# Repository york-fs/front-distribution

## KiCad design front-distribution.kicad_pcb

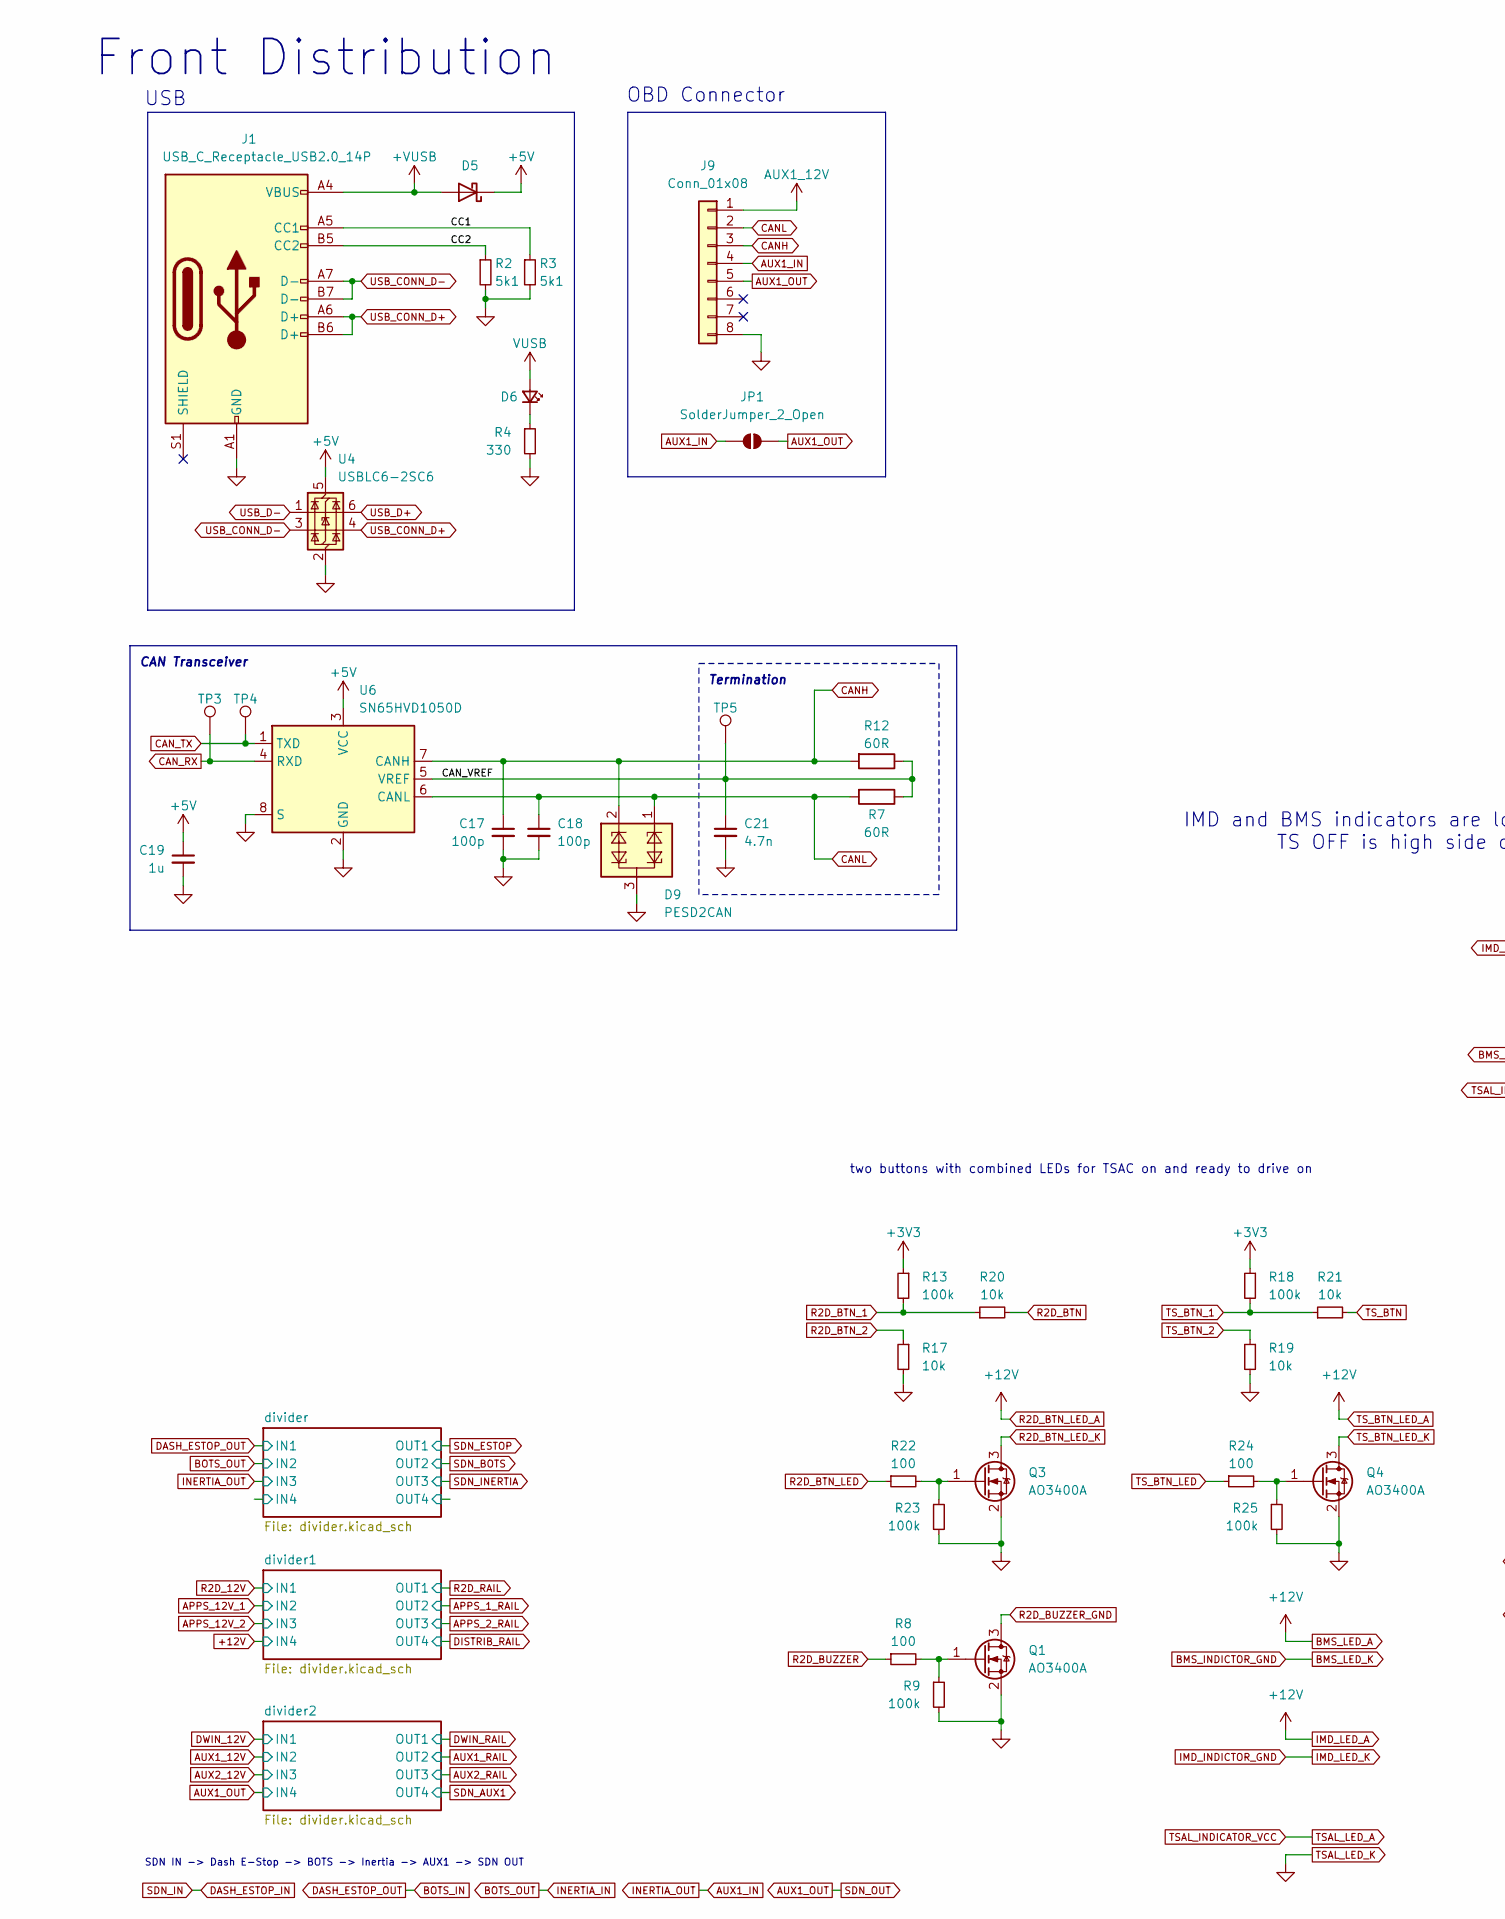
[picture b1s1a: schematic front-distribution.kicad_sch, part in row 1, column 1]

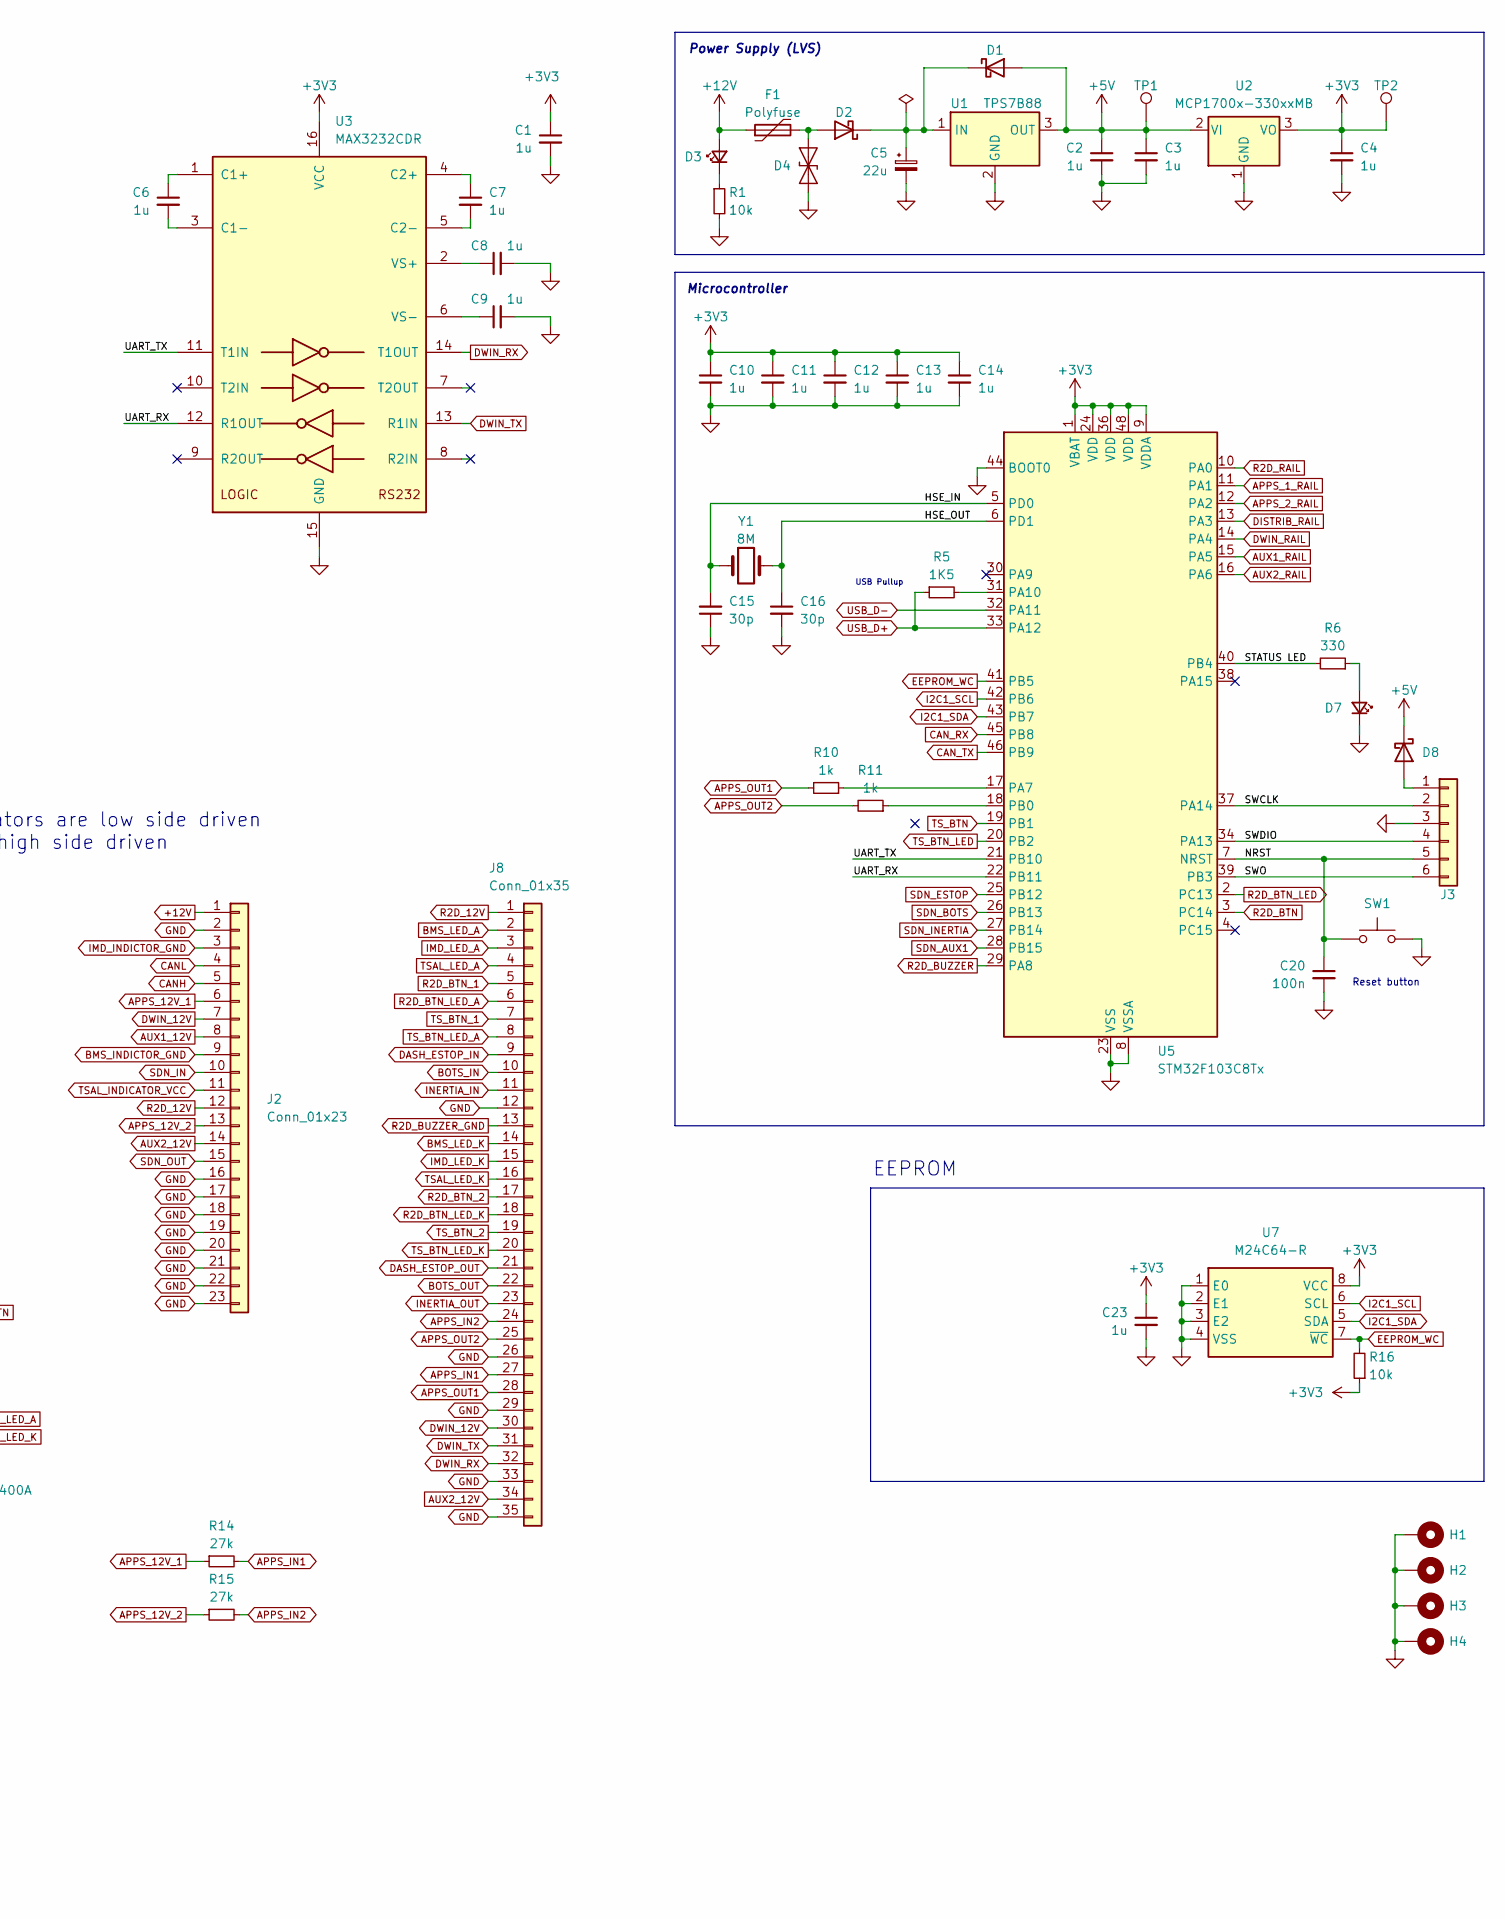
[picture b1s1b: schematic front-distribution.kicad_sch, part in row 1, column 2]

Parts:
C1, C2, C3, C4, C6, C7, C8, C9, C10, C11, C12, C13, C14, C19: 1u; C_0603_1608Metric; Mfr # CL10B105KB8NQNC
C5: 22u; CP_Elec_6.3x7.7; Mfr # EEEFK1J220XP
C15, C16: 30p; C_0603_1608Metric; Mfr # GQM1875C2E300GB12D
C17, C18: 100p; C_0603_1608Metric; Mfr # GCM1885C2A101JA16D
C20: 100n; C_0603_1608Metric; Mfr # CL10B104KB8NNNC
C21: 4.7n; C_0603_1608Metric; Mfr # CL10B105KB8NQNC
C23: 1u; C_0603_1608Metric
D1, D2, D5, D8: D_Schottky; D_SOD-323; Mfr # NSR0530H
D3, D7: LED_Small; LED_0603_1608Metric; Mfr # NCD0603R1
D4: SMAJ24CA; D_SMA; Mfr # SMAJ24CA
D6: LED_Small; LED_0603_1608Metric
D9: PESD2CAN; SOT-23; Mfr # PESD2CAN,215
F1: Polyfuse; C_0805_2012Metric; Mfr # 0805L010/24YR
H1, H2, H3, H4: MountingHole_Pad; MountingHole_3.2mm_M3_Pad_Via
J1: USB_C_Receptacle_USB2.0_14P; USB_C_Receptacle_G-Switch_GT-USB-7010ASV
J2: Conn_01x23; TE_770669-1
J3: Conn_01x06; IDC-Connector-2x3; Mfr # HX JN1.27-2x3P ZZ H4.9
J8: Conn_01x35; TE_776163-1
J9: Conn_01x08; TE_776280-1
JP1: SolderJumper_2_Open; SolderJumper-2_P1.3mm_Open_RoundedPad1.0x1.5mm
Q1, Q3, Q4: AO3400A; SOT-23
R1: 10k; R_0603_1608Metric; Mfr # 0603WAF1002T5E
R2, R3: 5k1; R_0603_1608Metric
R4: 330; R_0603_1608Metric
R5: 1K5; R_0603_1608Metric
R6: 330; R_0603_1608Metric; Mfr # 0603WAF3300T5E
R7, R12: 60R; R_1206_3216Metric
R8, R22, R24: 100; R_0603_1608Metric
R9, R23, R25: 100k; R_0603_1608Metric
R10, R11: 1k; R_0603_1608Metric
R13, R18: 100k; R_0603_1608Metric; Mfr # 0603WAF3300T5E
R14, R15: 27k; R_0603_1608Metric
R16, R20, R21: 10k; R_0603_1608Metric
R17, R19: 10k; R_0603_1608Metric; Mfr # 0603WAF3300T5E
SW1: SW_Push; SW_Push_1P1T_NO_Vertical_Wuerth_434133025816; Mfr # SKRPACE010
TP1, TP2, TP3, TP4, TP5: TestPoint; TestPoint_Keystone_5000-5004_Miniature
U1: TPS7B88; TO-252-2; Mfr # 595-TPS7B8850QKVURQ1
U2: MCP1700x-330xxMB; SOT-89-3; Mfr # MCP1700T-3302E/MB
U3: MAX3232CDR; SOIC-16_3.9x9.9mm_P1.27mm
U4: USBLC6-2SC6; SOT-23-6
U5: STM32F103C8Tx; LQFP-48_7x7mm_P0.5mm; Mfr # STM32F103C8T6
U6: SN65HVD1050D; SOIC-8_3.9x4.9mm_P1.27mm; Mfr # SN65HVD1050DR
U7: M24C64-R; SOIC-8_3.9x4.9mm_P1.27mm
Y1: 8M; Crystal_SMD_5032-2Pin_5.0x3.2mm; Mfr # X50328MSB2GI

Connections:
+3V3: C1.1, C4.1, C10.1, C11.1, C12.1, C13.1, C14.1, C23.1, R13.1, R16.1, R18.1, TP2.1, U2.3 (VO), U3.16 (VCC), U5.1 (VBAT), U5.9 (VDDA), U5.24 (VDD), U5.36 (VDD), U5.48 (VDD), U7.8 (VCC)
+5V: C2.1, C3.1, C19.1, D1.2 (A), D5.1 (K), D8.1 (K), TP1.1, U1.3 (OUT), U2.2 (VI), U4.5 (VBUS), U6.3 (VCC)
+12V: D3.2 (A), F1.1, J2.1, J8.2, J8.3, J8.6, J8.8; also elsewhere on the board
+VUSB: D5.2 (A), J1.A4 (VBUS), J1.A9 (VBUS), J1.B4 (VBUS), J1.B9 (VBUS)
/CAN_VREF: C21.1, R7.1, R12.1, TP5.1, U6.5 (VREF)
/CC1: J1.A5 (CC1), R3.1
/CC2: J1.B5 (CC2), R2.1
/HSE_IN: C15.2, U5.5 (PD0), Y1.1
/HSE_OUT: C16.1, U5.6 (PD1), Y1.2
/NRST: C20.1, J3.5, SW1.1, U5.7 (NRST)
/STATUS LED: R6.2, U5.40 (PB4)
/SWCLK: J3.2, U5.37 (PA14)
/SWDIO: J3.4, U5.34 (PA13)
/SWO: J3.6, U5.39 (PB3)
/UART_RX: U3.12 (R1OUT), U5.22 (PB11)
/UART_TX: U3.11 (T1IN), U5.21 (PB10)
APPS_1_RAIL: U5.11 (PA1); also elsewhere on the board
APPS_2_RAIL: U5.12 (PA2); also elsewhere on the board
APPS_12V_1: J2.6, R14.1; also elsewhere on the board
APPS_12V_2: J2.13, R15.1; also elsewhere on the board
APPS_IN1: J8.27, R14.2
APPS_IN2: J8.24, R15.2
APPS_OUT1: J8.28, R10.2
APPS_OUT2: J8.25, R11.2
AUX1_12V: J2.8, J9.1; also elsewhere on the board
AUX1_IN: J8.23, J9.4, JP1.2 (B); also elsewhere on the board
AUX1_OUT: J2.15, J9.5, JP1.1 (A); also elsewhere on the board
AUX1_RAIL: U5.15 (PA5); also elsewhere on the board
AUX2_12V: J2.14, J8.34; also elsewhere on the board
AUX2_RAIL: U5.16 (PA6); also elsewhere on the board
BMS_INDICTOR_GND: J2.9, J8.14
BOTS_IN: J8.10, J8.21; also elsewhere on the board
BOTS_OUT: J8.11, J8.22; also elsewhere on the board
CANH: C17.1, D9.2 (C2), J2.5, J9.3, R12.2, U6.7 (CANH)
CANL: C18.1, D9.1 (C1), J2.4, J9.2, R7.2, U6.6 (CANL)
CAN_RX: TP3.1, U5.45 (PB8), U6.4 (RXD)
CAN_TX: TP4.1, U5.46 (PB9), U6.1 (TXD)
DASH_ESTOP_IN: J2.10, J8.9
DISTRIB_RAIL: U5.13 (PA3); also elsewhere on the board
DWIN_12V: J2.7, J8.30; also elsewhere on the board
DWIN_RAIL: U5.14 (PA4); also elsewhere on the board
DWIN_RX: J8.32, U3.14 (T1OUT)
DWIN_TX: J8.31, U3.13 (R1IN)
EEPROM_WC: R16.2, U5.41 (PB5), U7.7 (~WC)
GND: C1.2, C2.2, C3.2, C4.2, C5.2, C8.2, C9.2, C10.2, C11.2, C12.2, C13.2, C14.2, C15.1, C16.2, C17.2, C18.2, C19.2, C20.2, C21.2, C23.2, D4.1 (A1), D7.1 (K), D9.3 (CC), H1.1, H2.1, H3.1, H4.1, J1.A1 (GND), J1.A12 (GND), J1.B1 (GND), J1.B12 (GND), J2.2, J2.16, J2.17, J2.18, J2.19, J2.20, J2.21, J2.22, J2.23, J3.3, J8.12, J8.16, J8.26, J8.29, J8.33, J8.35, J9.8, Q1.2 (S), Q3.2 (S), Q4.2 (S), R1.2, R2.2, R3.2, R4.2, R9.2, R17.2, R19.2, R23.2, R25.2, SW1.2, U1.2 (GND), U2.1 (GND), U3.15 (GND), U4.2 (GND), U5.8 (VSSA), U5.23 (VSS), U5.35 (VSS), U5.44 (BOOT0), U5.47 (VSS), U6.2 (GND), U6.8 (S), U7.1 (E0), U7.2 (E1), U7.3 (E2), U7.4 (VSS); also elsewhere on the board
I2C1_SCL: U5.42 (PB6), U7.6 (SCL)
I2C1_SDA: U5.43 (PB7), U7.5 (SDA)
IMD_INDICTOR_GND: J2.3, J8.15
unnamed: C5.1, D1.1 (K), D2.1 (K), U1.1 (IN)
unnamed: D2.2 (A), D4.2 (A2), F1.2
unnamed: D3.1 (K), R1.1
unnamed: D6.1 (K), R4.1
unnamed: D7.2 (A), R6.1
unnamed: D8.2 (A), J3.1
unnamed: Q1.1 (G), R8.2, R9.1
unnamed: Q3.1 (G), R22.2, R23.1
unnamed: Q4.1 (G), R24.2, R25.1
unnamed: C6.1, U3.1 (C1+)
unnamed: C6.2, U3.3 (C1-)
unnamed: C7.1, U3.4 (C2+)
unnamed: C7.2, U3.5 (C2-)
unnamed: C8.1, U3.2 (VS+)
unnamed: C9.1, U3.6 (VS-)
unnamed: R10.1, U5.17 (PA7)
unnamed: R5.2, U5.31 (PA10)
unnamed: R11.1, U5.18 (PB0)
R2D_12V: J2.12, J8.1; also elsewhere on the board
R2D_BTN: R20.2, U5.3 (PC14)
R2D_BTN_1: J8.5, R13.2, R20.1
R2D_BTN_2: J8.17, R17.1
R2D_BTN_LED: R22.1, U5.2 (PC13)
R2D_BTN_LED_K: J8.18, Q3.3 (D)
R2D_BUZZER: R8.1, U5.29 (PA8)
R2D_BUZZER_GND: J8.13, Q1.3 (D)
R2D_RAIL: U5.10 (PA0); also elsewhere on the board
SDN_AUX1: U5.28 (PB15); also elsewhere on the board
SDN_BOTS: U5.26 (PB13); also elsewhere on the board
SDN_ESTOP: U5.25 (PB12); also elsewhere on the board
SDN_INERTIA: U5.27 (PB14); also elsewhere on the board
TSAL_INDICATOR_VCC: J2.11, J8.4
TS_BTN: R21.2, U5.19 (PB1)
TS_BTN_1: J8.7, R18.2, R21.1
TS_BTN_2: J8.19, R19.1
TS_BTN_LED: R24.1, U5.20 (PB2)
TS_BTN_LED_K: J8.20, Q4.3 (D)
USB_CONN_D+: J1.A6 (D+), J1.B6 (D+), U4.4 (I/O2)
USB_CONN_D-: J1.A7 (D-), J1.B7 (D-), U4.3 (I/O2)
USB_D+: R5.1, U4.6 (I/O1), U5.33 (PA12)
USB_D-: U4.1 (I/O1), U5.32 (PA11)
VUSB: D6.2 (A)

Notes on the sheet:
two buttons with combined LEDs for TSAC on and ready to drive on
EEPROM
Reset button
Front Distribution
IMD and BMS indicators are low side driven TS OFF is high side driven
OBD Connector
Termination
SDN IN -> Dash E-Stop -> BOTS -> Inertia -> AUX1 -> SDN OUT
Power Supply (LVS)
Microcontroller
CAN Transceiver
USB
USB Pullup

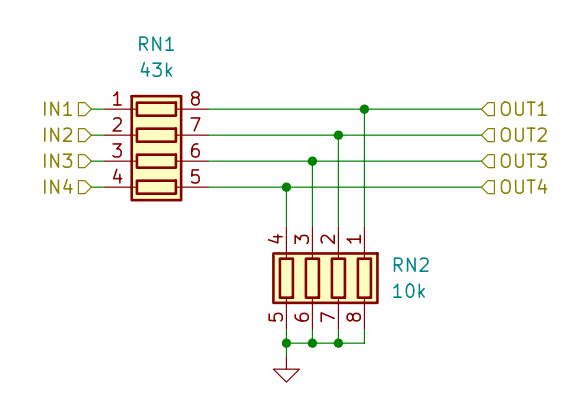
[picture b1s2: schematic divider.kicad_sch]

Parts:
RN1: 43k; R_Array_Convex_4x1206
RN2: 10k; R_Array_Convex_4x1206

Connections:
/divider/IN4: RN1.4 (R4.1)
/divider/OUT4: RN1.5 (R4.2), RN2.4 (R4.1)
AUX1_IN: RN1.3 (R3.1); also elsewhere on the board
BOTS_IN: RN1.1 (R1.1); also elsewhere on the board
BOTS_OUT: RN1.2 (R2.1); also elsewhere on the board
GND: RN2.5 (R4.2), RN2.6 (R3.2), RN2.7 (R2.2), RN2.8 (R1.2); also elsewhere on the board
SDN_BOTS: RN1.7 (R2.2), RN2.2 (R2.1); also elsewhere on the board
SDN_ESTOP: RN1.8 (R1.2), RN2.1 (R1.1); also elsewhere on the board
SDN_INERTIA: RN1.6 (R3.2), RN2.3 (R3.1); also elsewhere on the board

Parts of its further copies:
RN4, RN7: 43k; R_Array_Convex_4x1206
RN5, RN8: 10k; R_Array_Convex_4x1206

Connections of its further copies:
+12V: RN4.4 (R4.1); also elsewhere on the board
APPS_1_RAIL: RN4.7 (R2.2), RN5.2 (R2.1); also elsewhere on the board
APPS_2_RAIL: RN4.6 (R3.2), RN5.3 (R3.1); also elsewhere on the board
APPS_12V_1: RN4.2 (R2.1); also elsewhere on the board
APPS_12V_2: RN4.3 (R3.1); also elsewhere on the board
AUX1_12V: RN7.2 (R2.1); also elsewhere on the board
AUX1_OUT: RN7.4 (R4.1); also elsewhere on the board
AUX1_RAIL: RN7.7 (R2.2), RN8.2 (R2.1); also elsewhere on the board
AUX2_12V: RN7.3 (R3.1); also elsewhere on the board
AUX2_RAIL: RN7.6 (R3.2), RN8.3 (R3.1); also elsewhere on the board
DISTRIB_RAIL: RN4.5 (R4.2), RN5.4 (R4.1); also elsewhere on the board
DWIN_12V: RN7.1 (R1.1); also elsewhere on the board
DWIN_RAIL: RN7.8 (R1.2), RN8.1 (R1.1); also elsewhere on the board
GND: RN5.5 (R4.2), RN5.6 (R3.2), RN5.7 (R2.2), RN5.8 (R1.2), RN8.5 (R4.2), RN8.6 (R3.2), RN8.7 (R2.2), RN8.8 (R1.2); also elsewhere on the board
R2D_12V: RN4.1 (R1.1); also elsewhere on the board
R2D_RAIL: RN4.8 (R1.2), RN5.1 (R1.1); also elsewhere on the board
SDN_AUX1: RN7.5 (R4.2), RN8.4 (R4.1); also elsewhere on the board

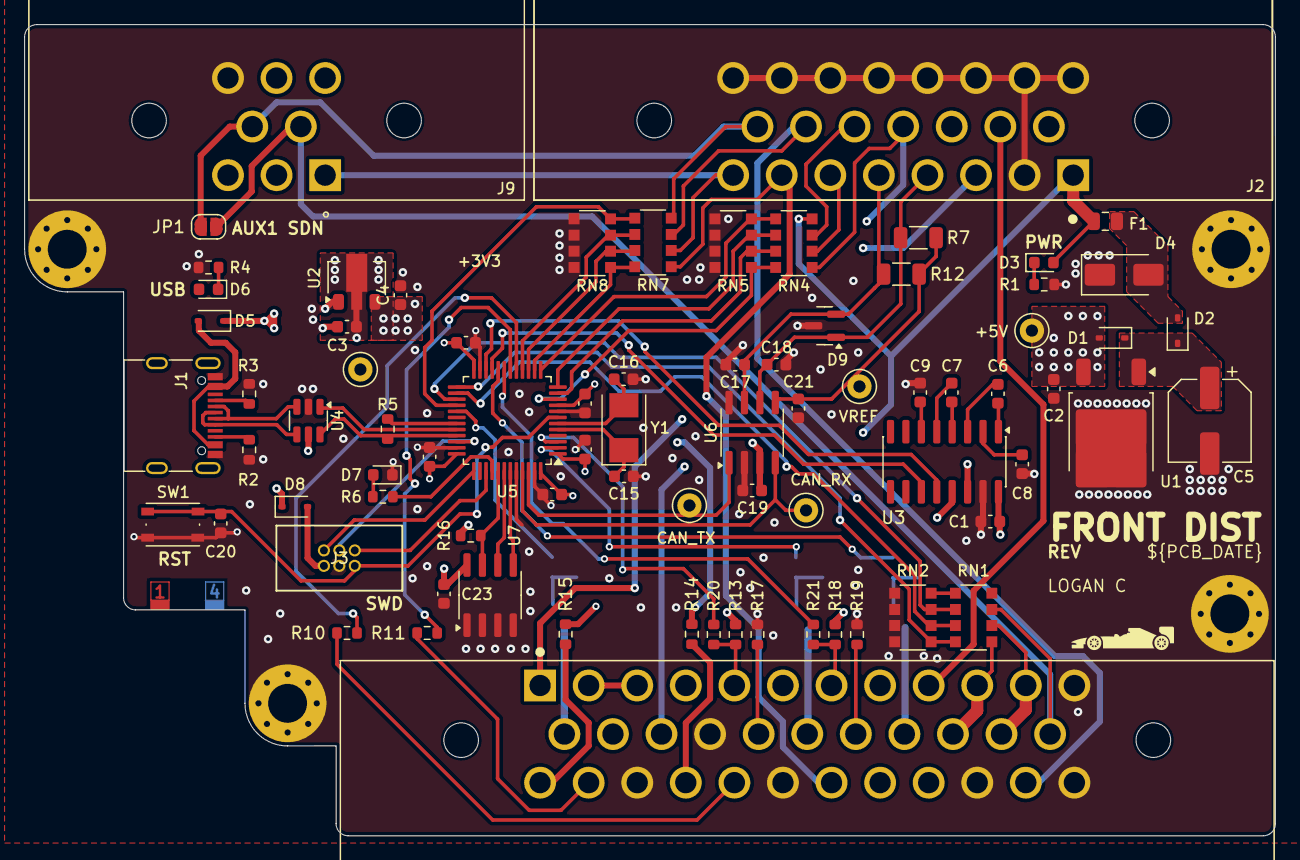
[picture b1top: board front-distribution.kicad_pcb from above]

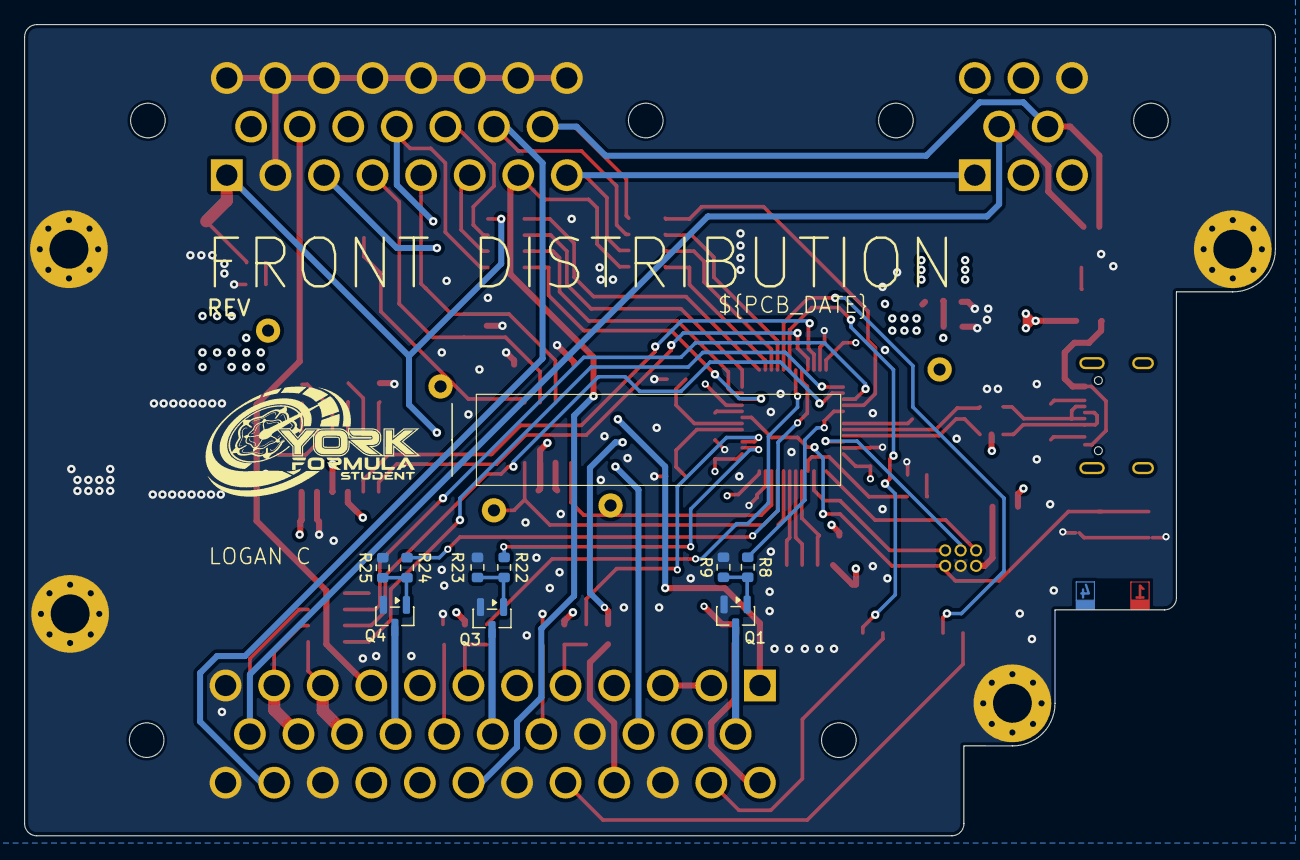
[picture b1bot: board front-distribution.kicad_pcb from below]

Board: 4 copper layers, 103.0 x 66.8 mm, 90 parts (9 on the bottom side), 90 nets.

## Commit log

2026-05-31 Revision A
2026-05-31 Updated revision variable
2026-06-07 Updated CAN termination resistors
2026-06-26 ci: Add KiCad CI
2026-06-30 kicad-library: Switch to an existent version
